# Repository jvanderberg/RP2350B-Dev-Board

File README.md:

# RP2350B-Dev-Board

This is an RP2350B Dev board that breaks out all 48 GPIO pins.

It follows the original footprint of the RP2040 dev board, but adds 10 pins on each side.

It is not pin compatible with the original RP2040, though a version that shares the same pinout, at least for the first 20 pins on each side would be interesting.

Pinout:

```
1	GPIO0	        60	VBUS
2	GPIO1	        59	VSYS
3	GPIO2	        58	GND
4	GPIO3	        57	3v3
5	GPIO4	        56	3v3_EN
6	GPIO5	        55	ADC_VREF
7	GPIO6	        54	GND
8	GPIO7	        53	GPIO47/ADC7
9	GPIO8	        52	GPIO46/ADC6
10	GPIO9	        51	GPIO45/ADC5
11	GND	            50	GND
12	GPIO10	        49	GPIO44/ADC4
13	GPIO11	        48	GPIO43/ADC3
14	GPIO12	        47	GPIO42/ADC2
15	GPIO13	        46	GPIO41/ADC1
16	GPIO14	        45	GPIO40/ADC0
17	GPIO15	        44	GPIO39
18	GPIO16	        43	GPIO38
19	GPIO17	        42	GPIO37
20	GPIO18	        41	GPIO36
21	GPIO19	        40	GPIO35
22	GND	            39	GND
23	GPIO20	        38	GPIO34
24	GPIO21	        37	GPIO33
25	GPIO22	        36	GPIO32
26	GPIO23	        35	GPIO31
27	GPIO24	        34	GPIO30
28	GPIO25	        33	GPIO29
29	GPIO26	        32	GPIO28
30	GPIO27	        31	RUN
```

## Production files for JLCPCB

The production files for JLCPCB are in the 'production' directory.

RP2350_Dev_board.zip is the zipped Gerber files.

bom.csv and positions.csv are the Bill of materials and placements files respectively.

These were produced with the 'Fabrication Toolkit' plugin, which you will need to install if you need to regenerate them.

## Source Designs

Thie design borrows from https://pro.easyeda.com/editor#id=a0a21c97b13d436db5579fc2a8b1625d, which is an RP2350A design. I adapted it for the RP2350B, but it shares most of the schematic, if not the PCB layout.

I also looked at the RP2350B reference designs available here: https://datasheets.raspberrypi.com/rp2350/Minimal-KiCAD.zip

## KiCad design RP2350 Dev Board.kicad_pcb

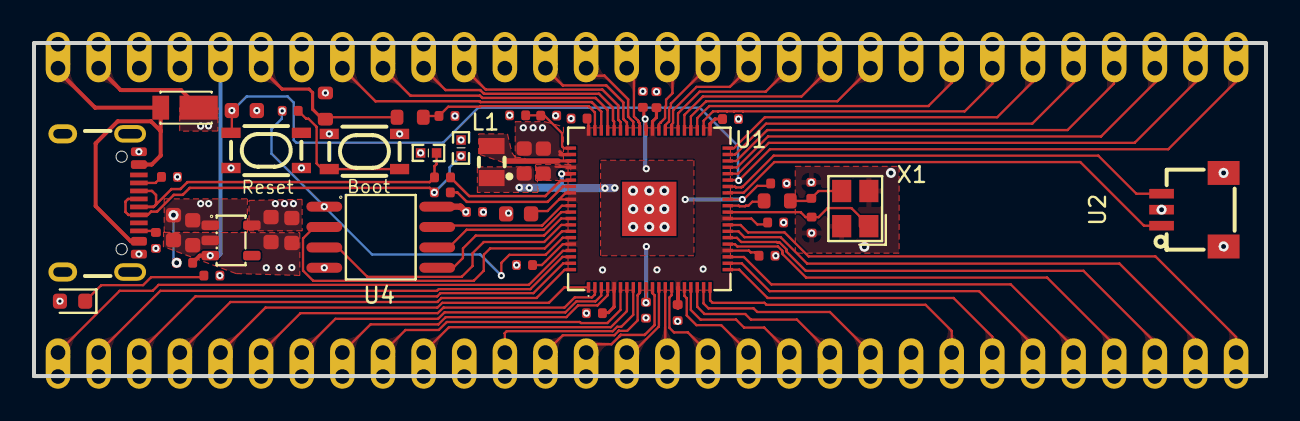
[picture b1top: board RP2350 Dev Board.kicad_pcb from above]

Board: 4 copper layers, 77.0 x 20.8 mm, 108 parts (0 on the bottom side), 78 nets.

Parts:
3V3_EN1, 3V31: Castellated Pad
ADC_VREF1: Castellated Pad
Boot1: K2-1808SN-A4SW-01; KEY-SMD_4P-L4.2-W3.2-P2.20-LS5.1-TL
C1, C2, C3, C4, C5, C6, C7, C8, C13, C14, C16, C36: 100nF; C_0402
C9, C15, C38, C39: 100nF; C_0603
C10, C12: 4.7uF; C_0603
C11, C19: 4.7uF; C_0402
C17, C18: 15pF; C_0402
C37, C40: 10uF; C_0603
D1: POWERDI-123_L2.8-W1.8-LS3.7-RD
D2, D3: RCLAMP0521P.TCT-MS; D0402-BI
GND1, GND2, GND3, GND4, GND4#2, GND6: Castellated Pad
GPI10: Castellated Pad
GPIO0, GPIO1, GPIO1#2, GPIO1#3, GPIO1#4, GPIO1#5, GPIO1#6, GPIO1#7, GPIO1#8, GPIO2, GPIO3, GPIO4, GPIO5, GPIO7, GPIO8, GPIO11, GPIO12, GPIO13, GPIO15, GPIO16, GPIO17, GPIO18, GPIO19, GPIO21, GPIO21#2, GPIO22, GPIO24, GPIO25, GPIO26, GPIO27, GPIO28, GPIO29, GPIO30, GPIO32, GPIO34, GPIO35, GPIO36, GPIO37, GPIO38, GPIO39, GPIO40, GPIO41, GPIO42, GPIO43, GPIO44, GPIO45, GPIO46: Castellated Pad
L1: IND-SMD_L2.0-W1.6_AOTA-B201610S3R3-101-T
PWR_LED1: Red; D_0603
R1, R4: 5.1kΩ; R_0402
R2, R3, R6: 33Ω; R_0402
R5: 1kΩ; R_0402
R7: 1Ω; R_0603
R8: 200Ω; R_0603
R11: 100kΩ; R_0402
R12: 2kΩ; R_0402
R28: 1kΩ; R_0603
RUN1: Castellated Pad
Reset1: K2-1808SN-A4SW-01; KEY-SMD_4P-L4.2-W3.2-P2.20-LS5.1-TL
U1: QFN-80_L10.0-W10.0-P0.40-TL-EP3.4
U2: HC-1.0-3PWT; CONN-SMD_SM03B-SRSS-TB-LF-SN-P
U3: SOT-23-5_L3.0-W1.7-P0.95-LS2.8-BR
U4: W25Q128; SOIC-8_L5.3-W5.3-P1.27-LS8.0-BL
USB1: USB-C-SMD_TYPE-C-6PIN-2MD-073
VBUS1: Castellated Pad
VSYS1: Castellated Pad
X1: CRYSTAL-SMD_4P-L3.2-W2.5-BL

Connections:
1V1: C2.1, C5.1, C10.2, C13.2, L1.2, U1.10 (DVDD), U1.32 (DVDD), U1.51 (DVDD), U1.65 (VREG_FB)
3V3: 3V31.57, C1.1, C3.1, C4.1, C6.1, C7.1, C8.2, C9.2, C12.2, C14.2, C16.2, C36.2, C38.1, C40.1, PWR_LED1.2, R6.1, R8.2, U1.5 (IOVDD), U1.15 (IOVDD), U1.24 (IOVDD), U1.29 (IOVDD), U1.41 (IOVDD), U1.50 (IOVDD), U1.60 (IOVDD), U1.64 (VREG_VIN), U1.68 (USB_OTP_VDD), U1.69 (QSPI_IOVDD), U1.76 (IOVDD), U3.5 (VOUT), U4.8 (VCC)
3V3_EN: 3V3_EN1.56, R11.2, U3.3 (CE)
/VREG_LX: L1.1, U1.63 (VREG_LX)
ADC_VREF: ADC_VREF1.55, R7.2, R8.1
GND: Boot1.3, Boot1.4, C1.2, C2.2, C3.2, C4.2, C5.2, C6.2, C7.2, C8.1, C9.1, C10.1, C11.1, C12.1, C13.1, C14.1, C15.1, C16.1, C17.2, C18.1, C19.2, C36.1, C37.2, C38.2, C39.2, C40.2, D2.1, D3.1, GND2.22, GND3.39, GND4.49, GND4#2.54, GND6.58, GPI10.11, R1.1, R4.1, R12.2, Reset1.3, Reset1.4, U1.62 (VREG_PGND), U1.81 (GND), U2.2, U2.4, U2.5, U3.2 (VSS), U4.4 (GND), USB1.1 (GND), USB1.12 (GND), USB1.13 (SHELL), USB1.14 (SHELL), X1.2 (GND), X1.4 (GND)
GPIO0: GPIO0.1, U1.77 (GPIO0)
GPIO1: GPIO1#2.2, U1.78 (GPIO1)
GPIO2: GPIO2.3, U1.79 (GPIO2)
GPIO3: GPIO3.4, U1.80 (GPIO3)
GPIO4: GPIO4.5, U1.1 (GPIO4)
GPIO5: GPIO5.6, U1.2 (GPIO5)
GPIO6: GPIO1#8.7, U1.3 (GPIO6)
GPIO7: GPIO7.8, U1.4 (GPIO7)
GPIO8: GPIO8.9, U1.6 (GPIO8)
GPIO9: GPIO1#7.10, U1.7 (GPIO9)
GPIO10: GND1.12, U1.8 (GPIO10)
GPIO11: GPIO11.13, U1.9 (GPIO11)
GPIO12: GPIO12.14, U1.11 (GPIO12)
GPIO13: GPIO13.15, U1.12 (GPIO13)
GPIO14: GPIO1#6.16, U1.13 (GPIO14)
GPIO15: GPIO15.17, U1.14 (GPIO15)
GPIO16: GPIO16.18, U1.16 (GPIO16)
GPIO17: GPIO17.19, U1.17 (GPIO17)
GPIO18: GPIO18.20, U1.18 (GPIO18)
GPIO19: GPIO19.21, U1.19 (GPIO19)
GPIO20: GPIO21.23, U1.20 (GPIO20)
GPIO21: GPIO21#2.24, U1.21 (GPIO21)
GPIO22: GPIO22.25, U1.22 (GPIO22)
GPIO23: GPIO1#5.26, U1.23 (GPIO23)
GPIO24: GPIO24.27, U1.25 (GPIO24)
GPIO25: GPIO25.28, U1.26 (GPIO25)
GPIO26: GPIO26.29, U1.27 (GPIO26)
GPIO27: GPIO27.30, U1.28 (GPIO27)
GPIO28: GPIO28.31, U1.36 (GPIO28)
GPIO29: GPIO29.33, U1.37 (GPIO29)
GPIO30: GPIO30.34, U1.38 (GPIO30)
GPIO31: GPIO1#4.1, GPIO1#4.35, U1.39 (GPIO31)
GPIO32: GPIO1.36, U1.40 (GPIO32)
GPIO33: GPIO32.37, U1.42 (GPIO33)
GPIO34: GPIO34.38, U1.43 (GPIO34)
GPIO35: GPIO35.40, U1.44 (GPIO35)
GPIO36: GPIO36.41, U1.45 (GPIO36)
GPIO37: GPIO37.42, U1.46 (GPIO37)
GPIO38: GPIO38.43, U1.47 (GPIO38)
GPIO39: GPIO39.44, U1.48 (GPIO39)
GPIO40/ADC0: GPIO40.45, U1.49 (GPIO40_ADC0)
GPIO41/ADC1: GPIO41.46, U1.52 (GPIO41_ADC1)
GPIO42/ADC2: GPIO42.47, U1.53 (GPIO42_ADC2)
GPIO43/ADC3: GPIO43.48, U1.54 (GPIO43_ADC3)
GPIO44/ADC4: GPIO44.50, U1.55 (GPIO44_ADC4)
GPIO45/ADC5: GPIO45.51, U1.56 (GPIO45_ADC5)
GPIO46/ADC6: GPIO46.52, U1.57 (GPIO46_ADC6)
GPIO47/ADC7: GPIO1#3.53, U1.58 (GPIO47_ADC7)
unnamed: Boot1.1, Boot1.2, R5.1
unnamed: C17.1, R28.1, X1.3
unnamed: PWR_LED1.1, R12.1
unnamed: C19.1, R7.1, U1.59 (ADC_AVDD)
unnamed: U1.71 (QSPI_SCLK), U4.6 (CLK)
unnamed: U1.72 (QSPI_SD0), U4.5 (DI)
unnamed: U1.74 (QSPI_SD1), U4.2 (DO)
unnamed: U1.73 (QSPI_SD2), U4.3 (IO2)
unnamed: U1.70 (QSPI_SD3), U4.7 (IO3)
unnamed: R5.2, U1.75 (QSPI_SS), U4.1 (CS#)
unnamed: U1.33 (SWCLK), U2.1
unnamed: U1.34 (SWDIO), U2.3
unnamed: R2.1, U1.66 (USB_DM)
unnamed: R3.1, U1.67 (USB_DP)
unnamed: C11.2, R6.2, U1.61 (VREG_AVDD)
unnamed: C18.2, U1.30 (XIN), X1.1
unnamed: R28.2, U1.31 (XOUT)
unnamed: R1.2, USB1.4 (CC1)
unnamed: R4.2, USB1.10 (CC2)
RUN: C15.2, RUN1.30, Reset1.1, U1.35 (RUN)
USB2_D+: D3.2, R3.2, USB1.6 (DP1), USB1.8 (DP2)
USB2_D-: D2.2, R2.2, USB1.5 (DN2), USB1.7 (DN1)
VBUS: D1.2, USB1.2 (VBUS), USB1.11 (VBUS), VBUS1.60
VSYS: C37.1, C39.1, D1.1, R11.1, U3.1 (VIN), VSYS1.59

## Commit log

2025-07-17 Final
2025-07-17 Readme correction
2025-07-31 Fix readme pinout
